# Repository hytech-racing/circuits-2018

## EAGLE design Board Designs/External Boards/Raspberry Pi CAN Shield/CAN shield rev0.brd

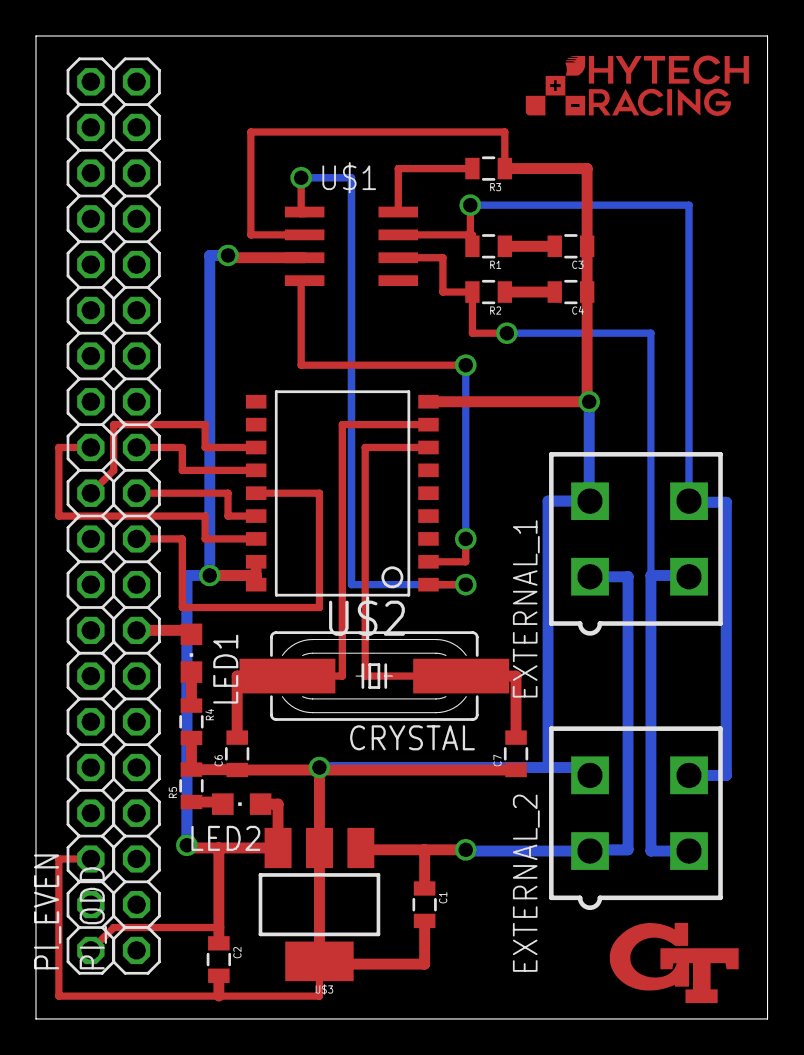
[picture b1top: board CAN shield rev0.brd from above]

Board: 2 copper layers, 40.6 x 54.6 mm, 21 parts (0 on the bottom side), 20 nets.

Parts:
C1: .22uF; 0805
C2: .1uF; 0805
C3, C4: 560pF; 0805
C6, C7: 22pF; 0805
CRYSTAL: 16MHz; HC49UP
EXTERNAL_1, EXTERNAL_2: MINIFIT_5566-4
LED1, LED2: LED-805
PI_EVEN: 1X20
PI_ODD: 1X20
R1, R2: 100; 0805
R3: 4.7k; 0805
R4, R5: 150; 0805
U$1: MCP2551; SOIC-08
U$2: MCP2515SMD; SOIC-18W
U$3: SOT223

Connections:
5VSUPPLY: C2.1, LED2.A, PI_EVEN.1, U$1.3, U$2.17, U$2.18, U$3.3
CAN-H: EXTERNAL_1.4, EXTERNAL_2.4, R1.2, U$1.7
CAN-L: EXTERNAL_1.3, EXTERNAL_2.3, R2.2, U$1.6
CS: PI_EVEN.12, U$2.16
GND: C1.2, C2.2, C3.1, C4.1, C6.1, C7.1, EXTERNAL_1.2, EXTERNAL_2.2, PI_EVEN.3, R3.1, R4.2, R5.2, U$1.2, U$2.9, U$3.2, U$3.4
INT: PI_EVEN.11, U$2.12
unnamed: LED1.C, R4.1
unnamed: PI_ODD.11, U$2.15
unnamed: PI_ODD.10, U$2.14
unnamed: PI_ODD.12, U$2.13
unnamed: C1.1, EXTERNAL_1.1, EXTERNAL_2.1, U$3.1
unnamed: LED1.A, PI_ODD.8
unnamed: LED2.C, R5.1
unnamed: C6.2, CRYSTAL.2, U$2.8
unnamed: U$1.1, U$2.1
unnamed: U$1.4, U$2.2
unnamed: C3.2, R1.1
unnamed: C7.2, CRYSTAL.1, U$2.7
unnamed: R3.2, U$1.8
unnamed: C4.2, R2.1

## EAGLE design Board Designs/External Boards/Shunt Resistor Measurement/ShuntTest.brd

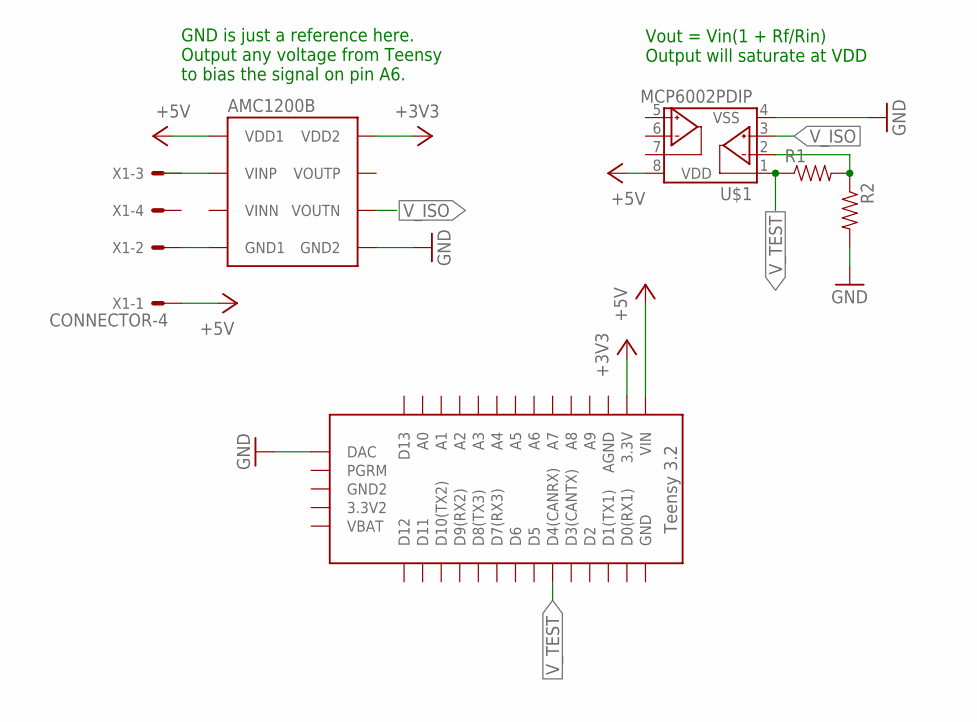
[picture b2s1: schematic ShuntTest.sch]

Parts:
R1, R2: RESISTOR0402; 0402-RES
U$1: MCP6002PDIP; DIL08
U$2: TEENSY_3.2_EXT
U$3: AMC1200B
X1: CONNECTOR-4; MINIFIT_5566-4

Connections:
+3V3: U$2.3.3V, U$3.VDD2
+5V: U$1.8 (VDD), U$2.VIN, U$3.VDD1, X1.1
GND: R2.2, U$1.4 (VSS), U$2.DAC, U$3.GND2
unnamed: U$3.GND1, X1.2
unnamed: U$3.VINP, X1.3
unnamed: R1.2, R2.1, U$1.2 (VINA-)
V_ISO: U$1.3 (VINA+), U$3.VOUTN
V_TEST: R1.1, U$1.1 (VOUTA), U$2.D4(CANRX)

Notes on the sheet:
Vout = Vin(1 + Rf/Rin) Output will saturate at VDD
GND is just a reference here. Output any voltage from Teensy to bias the signal on pin A6.

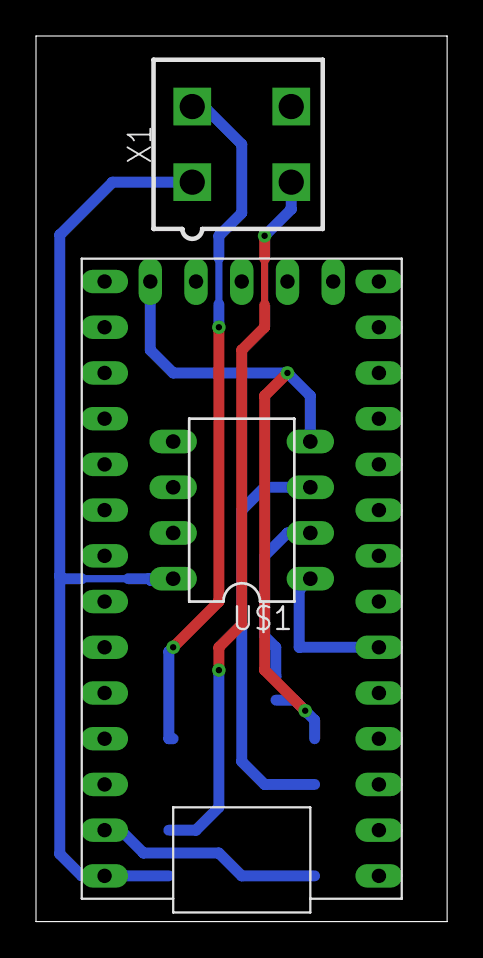
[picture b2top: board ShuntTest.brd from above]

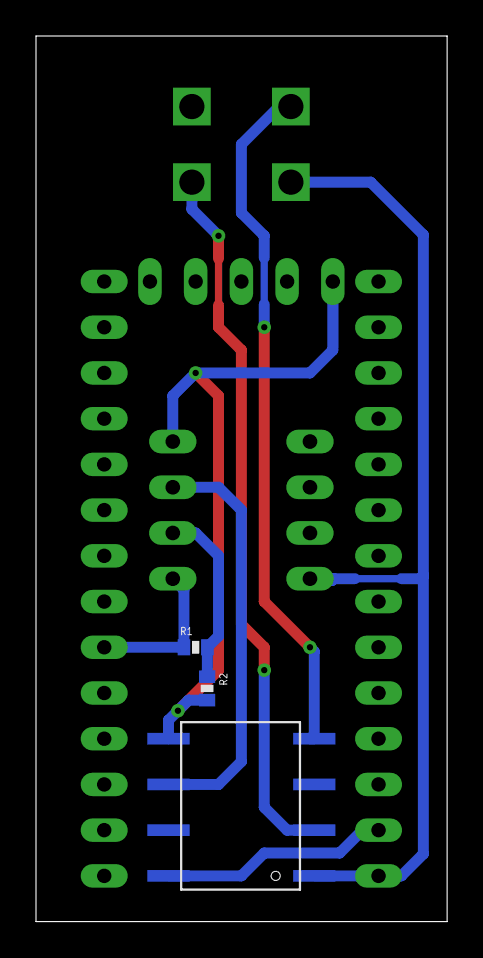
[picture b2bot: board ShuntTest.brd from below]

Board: 2 copper layers, 22.8 x 49.2 mm, 6 parts (3 on the bottom side), 8 nets.

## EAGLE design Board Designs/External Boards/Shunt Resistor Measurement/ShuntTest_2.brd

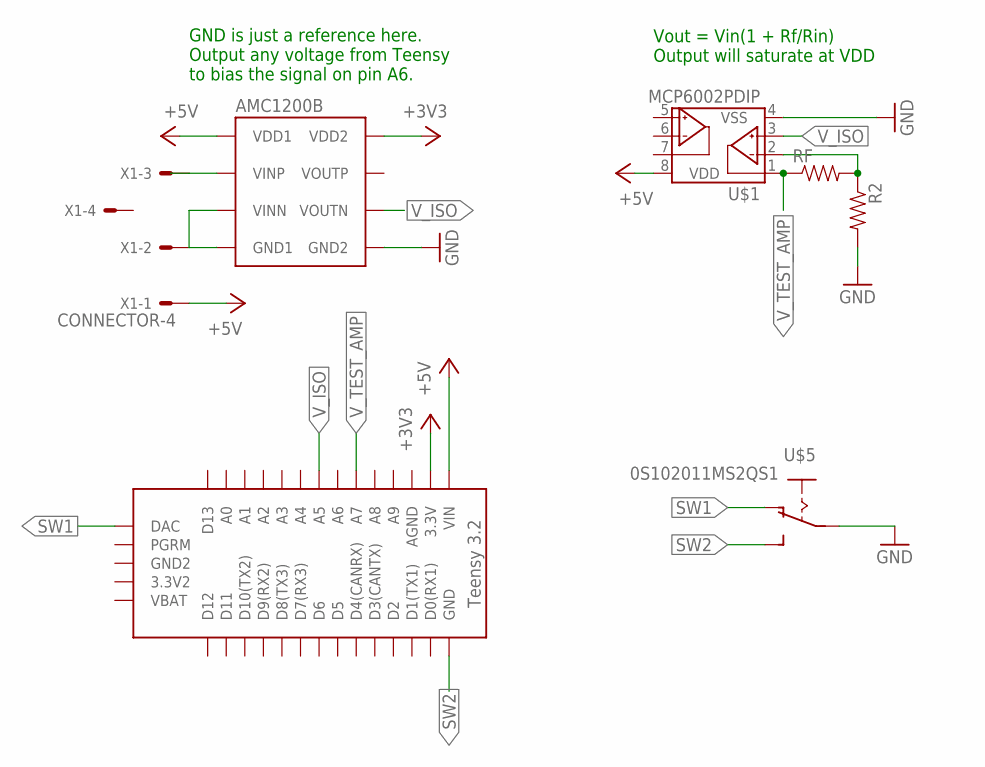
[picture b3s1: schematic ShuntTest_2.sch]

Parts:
R2: RESISTOR0402; 0402-RES
RF: RESISTOR0402; 0402-RES
U$1: MCP6002PDIP; DIL08
U$2: TEENSY_3.2_EXT
U$3: AMC1200B
U$5: 0S102011MS2QS1
X1: CONNECTOR-4; MINIFIT_5566-4

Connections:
+3V3: U$2.3.3V, U$3.VDD2
+5V: U$1.8 (VDD), U$2.VIN, U$3.VDD1, X1.1
GND: R2.2, U$1.4 (VSS), U$3.GND2, U$5.P$2
unnamed: U$3.GND1, U$3.VINN, X1.2
unnamed: U$3.VINP, X1.3
unnamed: R2.1, RF.2, U$1.2 (VINA-)
SW1: U$2.DAC, U$5.P$1 (O)
SW2: U$2.GND, U$5.P$3 (S)
V_ISO: U$1.3 (VINA+), U$2.A5, U$3.VOUTN
V_TEST_AMP: RF.1, U$1.1 (VOUTA), U$2.A7

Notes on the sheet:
Vout = Vin(1 + Rf/Rin) Output will saturate at VDD
GND is just a reference here. Output any voltage from Teensy to bias the signal on pin A6.

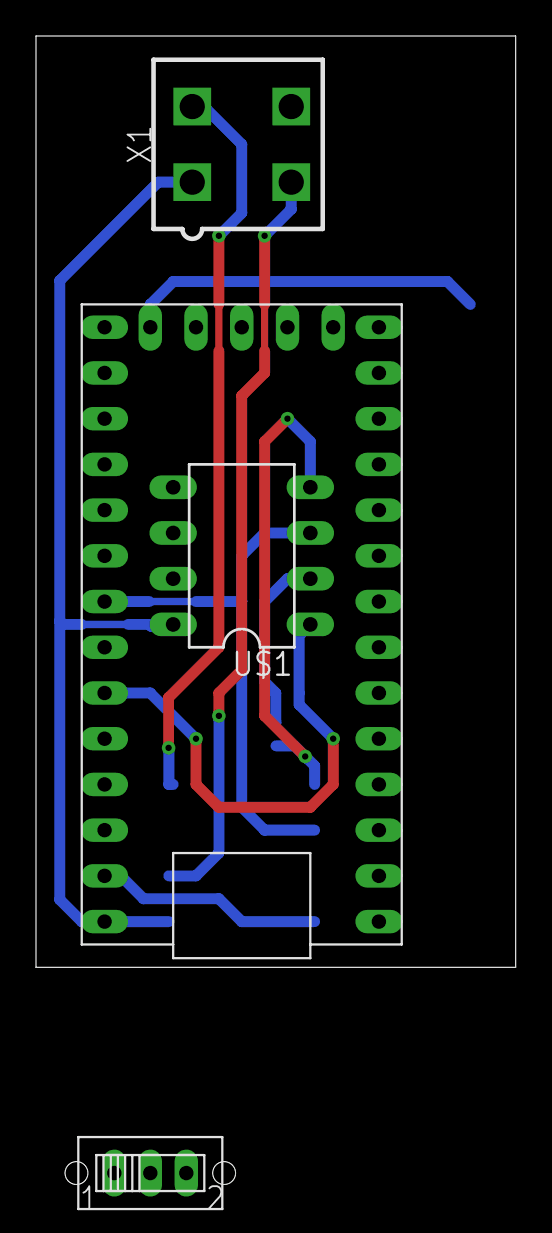
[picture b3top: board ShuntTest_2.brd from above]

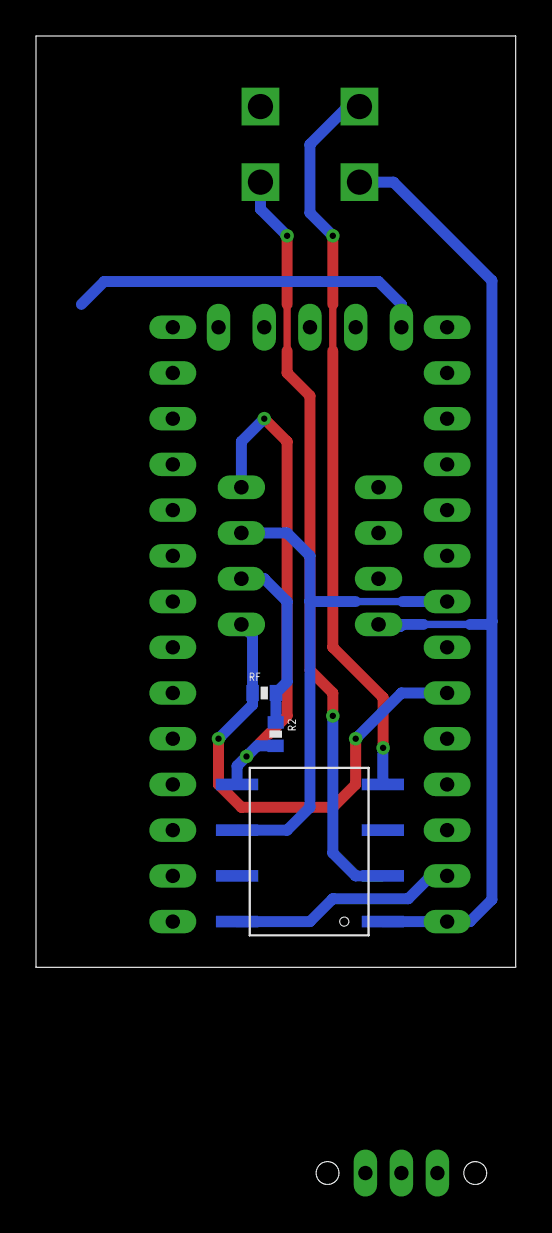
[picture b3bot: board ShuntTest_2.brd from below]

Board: 2 copper layers, 26.6 x 51.7 mm, 7 parts (3 on the bottom side), 10 nets.

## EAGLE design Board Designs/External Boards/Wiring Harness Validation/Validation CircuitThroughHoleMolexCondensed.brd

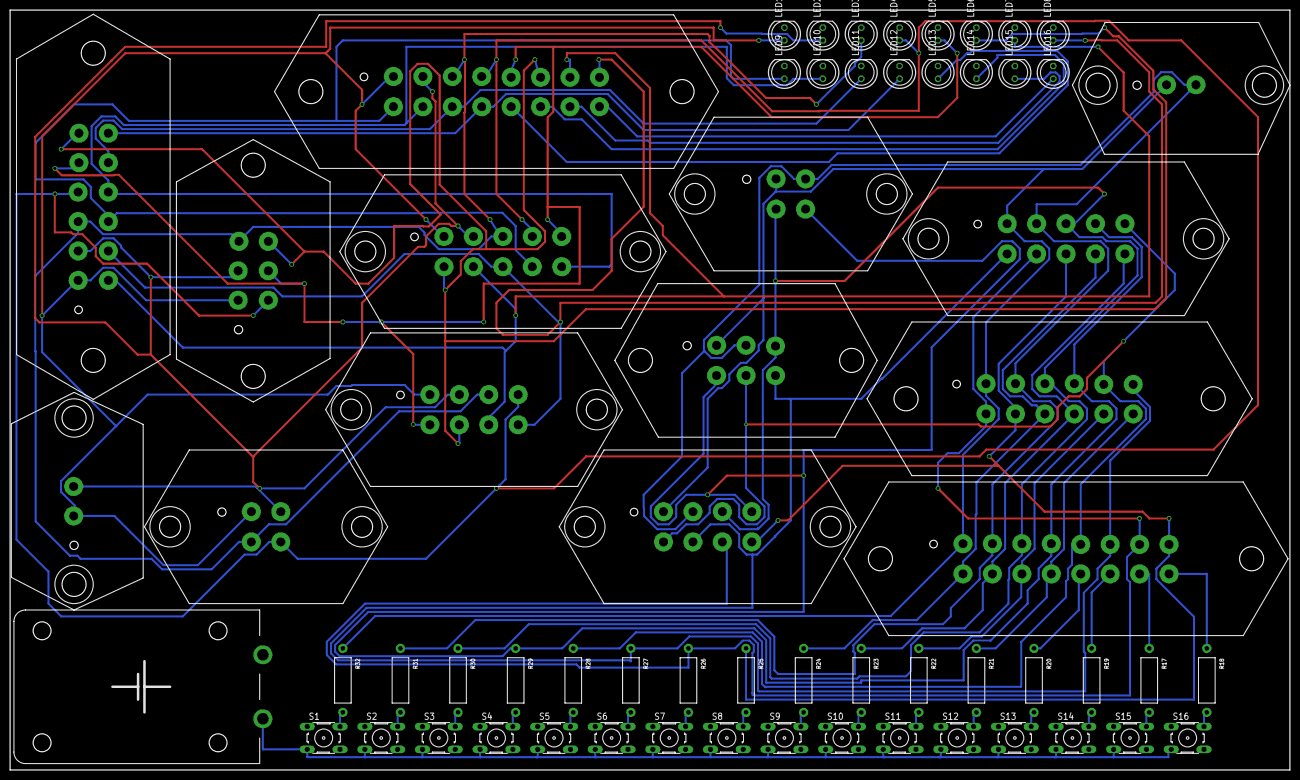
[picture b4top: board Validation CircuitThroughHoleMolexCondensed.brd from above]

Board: 2 copper layers, 254.0 x 150.8 mm, 63 parts (0 on the bottom side), 50 nets.

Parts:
LED1, LED2, LED3, LED4, LED5, LED6, LED7, LED8, LED9, LED10, LED11, LED12, LED13, LED14, LED15, LED16: LED-5MM
R17, R18, R19, R20, R21, R22, R23, R24, R25, R26, R27, R28, R29, R30, R31, R32: AXIAL-0.5
S1, S2, S3, S4, S5, S6, S7, S8, S9, S10, S11, S12, S13, S14, S15, S16: B3F-10XX
U$1, U$13: MX150L-4PINS; MX150L_VERTICAL-4
U$2, U$12: MX150L-6PINS; MX150L_VERTICAL-6
U$3, U$14: MX150L-2PINS; MX150L_VERTICAL-2
U$4, U$11: MX150L-8PINS; MX150L_VERTICAL-8
U$5, U$10: MX150L-10PINS; MX150L_VERTICAL-10
U$6, U$9: MX150L-12PINS; MX150L_VERTICAL-12
U$7, U$8: MX150L-16PINS; MX150L-VERTICAL-16
U$16: 1291-79

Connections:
GND: LED1.A, U$8.1, U$9.1, U$10.1, U$11.1, U$12.1, U$13.1, U$14.1
unnamed: S1.3, S2.3, S3.3, S4.3, S5.3, S6.3, S7.3, S8.3, S9.3, S10.3, S11.3, S12.3, S13.3, S14.3, S15.3, S16.3, U$16.+
unnamed: LED16.A, U$8.16
unnamed: LED8.A, U$8.8, U$9.8, U$10.8, U$11.8
unnamed: LED15.A, U$8.15
unnamed: LED14.A, U$8.14
unnamed: LED13.A, U$8.13
unnamed: LED12.A, U$8.12, U$9.12
unnamed: LED11.A, U$8.11, U$9.11
unnamed: LED10.A, U$8.10, U$9.10, U$10.10
unnamed: LED9.A, U$8.9, U$9.9, U$10.9
unnamed: LED7.A, U$8.7, U$9.7, U$10.7, U$11.7
unnamed: LED6.A, U$8.6, U$9.6, U$10.6, U$11.6, U$12.6
unnamed: LED5.A, U$8.5, U$9.5, U$10.5, U$11.5, U$12.5
unnamed: LED4.A, U$8.4, U$9.4, U$10.4, U$11.4, U$12.4, U$13.4
unnamed: LED3.A, U$8.3, U$9.3, U$10.3, U$11.3, U$12.3, U$13.3
unnamed: LED2.A, U$8.2, U$9.2, U$10.2, U$11.2, U$12.2, U$13.2, U$14.2
unnamed: LED1.K, LED2.K, LED3.K, LED4.K, LED5.K, LED6.K, LED7.K, LED8.K, LED9.K, LED10.K, LED11.K, LED12.K, LED13.K, LED14.K, LED15.K, LED16.K, U$16.-
unnamed: R32.P$2, S1.2
unnamed: R31.P$2, S2.2
unnamed: R30.P$2, S3.2
unnamed: R29.P$2, S4.2
unnamed: R28.P$2, S5.2
unnamed: R27.P$2, S6.2
unnamed: R26.P$2, S7.2
unnamed: R25.P$2, S8.2
unnamed: R24.P$2, S9.2
unnamed: R23.P$2, S10.2
unnamed: R22.P$2, S11.2
unnamed: R21.P$2, S12.2
unnamed: R20.P$2, S13.2
unnamed: R19.P$2, S14.2
unnamed: R17.P$2, S15.2
unnamed: R18.P$2, S16.2
PIN1: R32.P$1, U$1.1, U$2.1, U$3.1, U$4.1, U$5.1, U$6.1, U$7.1
PIN2: R31.P$1, U$1.2, U$2.2, U$3.2, U$4.2, U$5.2, U$6.2, U$7.2
PIN3: R30.P$1, U$1.3, U$2.3, U$4.3, U$5.3, U$6.3, U$7.3
PIN4: R29.P$1, U$1.4, U$2.4, U$4.4, U$5.4, U$6.4, U$7.4
PIN5: R28.P$1, U$2.5, U$4.5, U$5.5, U$6.5, U$7.5
PIN6: R27.P$1, U$2.6, U$4.6, U$5.6, U$6.6, U$7.6
PIN7: R26.P$1, U$4.7, U$5.7, U$6.7, U$7.7
PIN8: R25.P$1, U$4.8, U$5.8, U$6.8, U$7.8
PIN9: R24.P$1, U$5.9, U$6.9, U$7.9
PIN10: R23.P$1, U$5.10, U$6.10, U$7.10
PIN11: R22.P$1, U$6.11, U$7.11
PIN12: R21.P$1, U$6.12, U$7.12
PIN13: R20.P$1, U$7.13
PIN14: R19.P$1, U$7.14
PIN15: R17.P$1, U$7.15
PIN16: R18.P$1, U$7.16

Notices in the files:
parts and their libraries:
SparkFun-FreqCtrl: Licensing: Creative Commons ShareAlike 4.0 International - https://creativecommons.org/licenses/by-sa/4.0
